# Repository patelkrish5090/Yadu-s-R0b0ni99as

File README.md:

# Yadu-s-R0b0ni99as

## Members

### 1) Yadu Krishnan (Mechanical) (Team Lead)
### 2) Grace Paul (Mechanical)
### 3) Nilavroh Bandyopadhyay (Electronics)
### 4) Tilak Kamani (Electronics)
### 5) Krish Patel (Autonomous)

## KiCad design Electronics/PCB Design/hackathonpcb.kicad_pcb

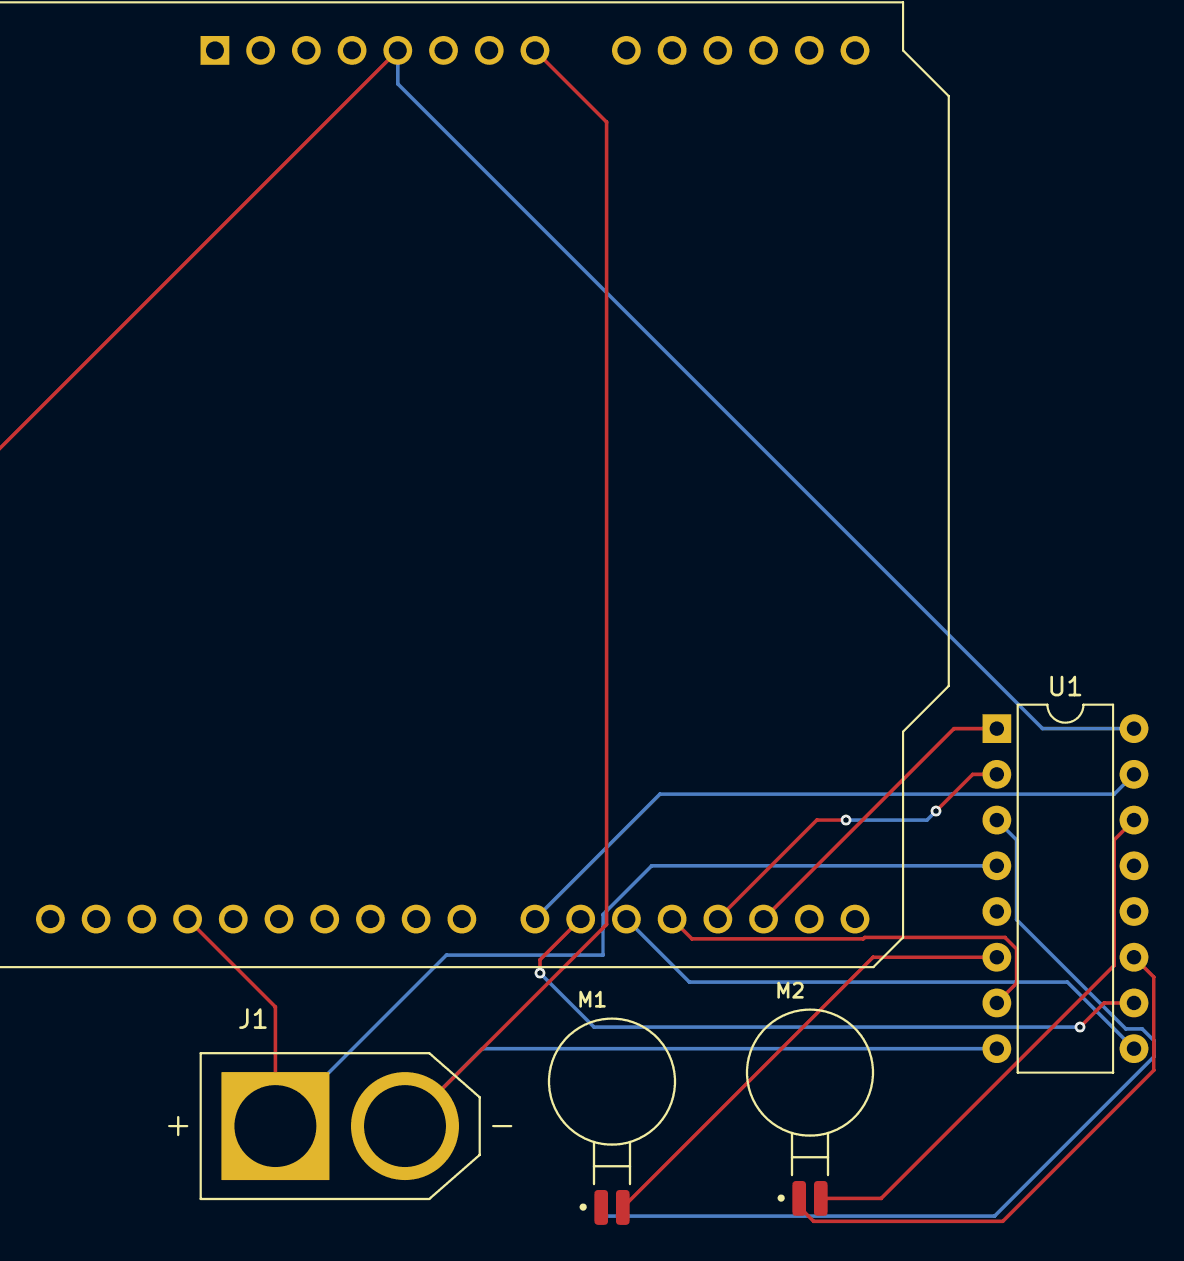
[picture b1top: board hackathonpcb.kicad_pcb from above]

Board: 2 copper layers, 5 parts (0 on the bottom side), 13 nets.

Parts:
Ard1: Arduino_UNO_R3
J1: XT60-M; AMASS_XT60-M
M1, M2: C0720B001F; XDCR_C0720B001F
U1: L293D; DIP-16_W7.62mm

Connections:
/5V: Ard1.5 (+5V), U1.16 (VCC1)
/D2: Ard1.17 (D2), U1.1 (EN1,2)
/D3: Ard1.18 (D3), U1.2 (1A)
/D4: Ard1.19 (D4), U1.7 (2A)
/D5: Ard1.20 (D5), U1.9 (EN3,4)
/D6: Ard1.21 (D6), U1.10 (3A)
/D7: Ard1.22 (D7), U1.15 (4A)
/GND: Ard1.29 (GND), J1.P (POS), U1.4 (GND)
/M11: M1.1 (V+), U1.3 (1Y)
/M12: M1.2 (V-), U1.6 (2Y)
/M21: M2.1 (V+), U1.11 (3Y)
/M22: M2.2 (V-), U1.14 (4Y)
/VCC: Ard1.8 (VIN), J1.N (NEG), U1.8 (VCC2)

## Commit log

2024-08-11 final work
2024-08-11 PCB Design Added
